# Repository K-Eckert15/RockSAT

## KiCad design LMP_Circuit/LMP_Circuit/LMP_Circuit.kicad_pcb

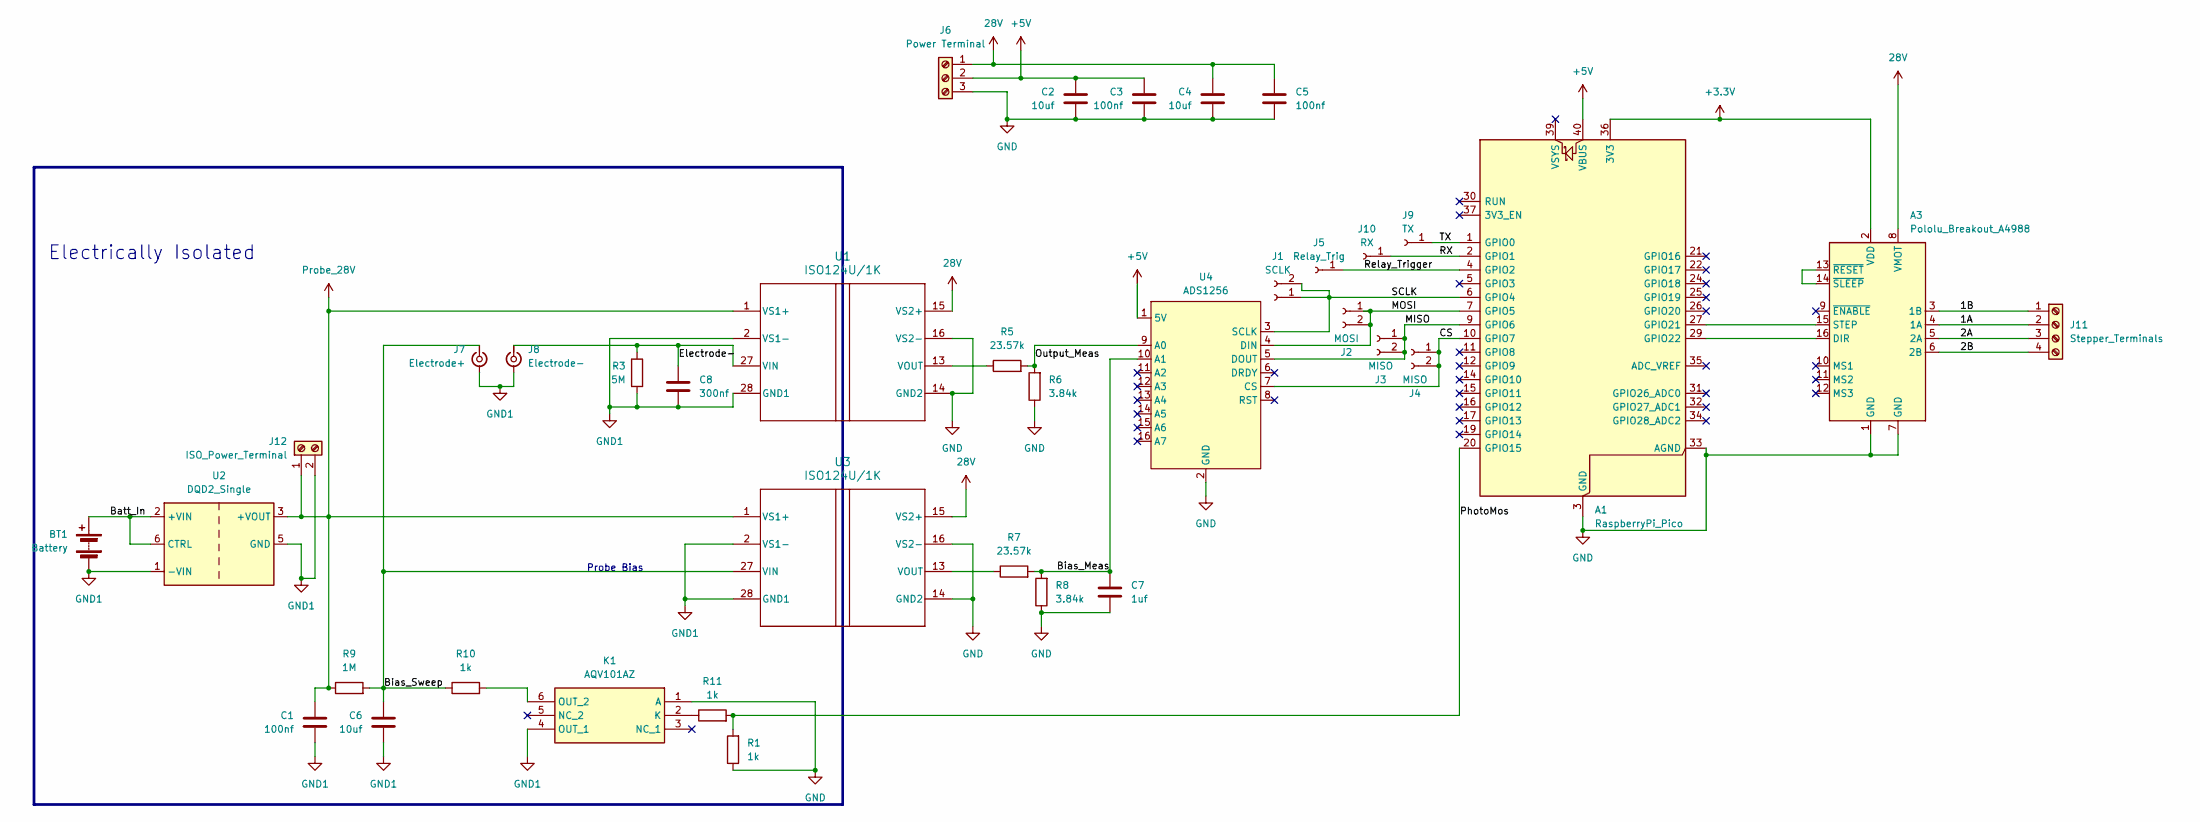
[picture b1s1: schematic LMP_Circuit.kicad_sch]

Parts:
A1: RaspberryPi_Pico; RaspberryPi_Pico_Common_Unspecified
A3: Pololu_Breakout_A4988; Pololu_Breakout-16_15.2x20.3mm
BT1: Battery; TerminalBlock_4Ucon_1x02_P3.50mm_Horizontal
C1, C3, C5: 100nf; C_0603_1608Metric; Manufacturer_Part_Number CC0603KRX7R9BB104
C2, C4, C6: 10uf; C_0603_1608Metric; Manufacturer_Part_Number GRM188R6YA106MA73D
C7: 1uf; C_0603_1608Metric; Manufacturer_Part_Number UMK107AB7105KA-T
C8: 300nf; C_0603_1608Metric; Manufacturer_Part_Number CGA3E3X7R1H334K080AB
J1: SCLK; PinHeader_1x02_P1.00mm_Vertical
J2: MOSI; PinHeader_1x02_P1.00mm_Vertical
J3, J4: MISO; PinHeader_1x02_P1.00mm_Vertical
J5: Relay_Trig; PinHeader_1x01_P1.00mm_Vertical
J6: Power Terminal; TerminalBlock_4Ucon_1x03_P3.50mm_Horizontal; Manufacturer_Part_Number 1984620
J7: Electrode+; SMA_Amphenol_901-143_Horizontal
J8: Electrode-; BNC_TEConnectivity_1478035_Horizontal
J9: TX; PinHeader_1x01_P1.00mm_Vertical
J10: RX; PinHeader_1x01_P1.00mm_Vertical
J11: Stepper_Terminals; TerminalBlock_4Ucon_1x04_P3.50mm_Horizontal; Manufacturer_Part_Number 1984633
J12: ISO_Power_Terminal; TerminalBlock_4Ucon_1x02_P3.50mm_Horizontal; Manufacturer_Part_Number ED555/2DS
K1: AQV101AZ; SOP254P960X390-6N; Mouser Part Number 769-AQV101AZ
R1, R10, R11: 1k; R_0603_1608Metric_Pad0.98x0.95mm_HandSolder; Manufacturer_Part_Number RMCF0603FT1K00
R3: 5M; R_0603_1608Metric_Pad0.98x0.95mm_HandSolder
R5, R7: 23.57k; R_0603_1608Metric_Pad0.98x0.95mm_HandSolder; Manufacturer_Part_Number RN73R1JTTD2342B25
R6, R8: 3.84k; R_0603_1608Metric_Pad0.98x0.95mm_HandSolder; Manufacturer_Part_Number ERA-3AEB3831V
R9: 1M; R_0603_1608Metric_Pad0.98x0.95mm_HandSolder; Manufacturer_Part_Number CRCW06031M00FKEA
U1, U3: ISO124U/1K; ISO124U
U2: DQD2_Single; DQD20
U4: ADS1256

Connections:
28V: A3.8 (VMOT), C4.1, C5.1, J6.1, U1.15 (VS2+), U3.15 (VS2+)
+3.3V: A1.36 (3V3), A3.2 (VDD)
+5V: A1.40 (VBUS), C2.1, C3.1, J6.2, U4.1 (5V)
/1A: A3.4 (1A), J11.2
/1B: A3.3 (1B), J11.1
/2A: A3.5 (2A), J11.3
/2B: A3.6 (2B), J11.4
/Bias_Meas: C7.2, R7.2, R8.2, U4.10 (A1)
/Bias_Sweep: C6.2, J7.1 (In), R9.2, R10.1, U3.27 (VIN)
/CS: A1.10 (GPIO7), J4.1, J4.2, U4.7 (CS)
/Electrode-: C8.2, J8.1 (In), R3.1, U1.27 (VIN)
/MISO: A1.9 (GPIO6), J3.1, J3.2, U4.5 (DOUT)
/MOSI: A1.7 (GPIO5), J2.1, J2.2, U4.4 (DIN)
/Output_Meas: R5.2, R6.2, U4.9 (A0)
/PhotoMos: A1.20 (GPIO15), R1.2, R11.2
/RX: A1.2 (GPIO1), J10.1
/Relay_Trigger: A1.4 (GPIO2), J5.1
/SCLK: A1.6 (GPIO4), J1.1, J1.2, U4.3 (SCLK)
/TX: A1.1 (GPIO0), J9.1
GND: A1.3 (GND), A1.8 (GND), A1.13 (GND), A1.18 (GND), A1.23 (GND), A1.28 (GND), A1.33 (AGND), A1.38 (GND), A3.1 (GND), A3.7 (GND), C2.2, C3.2, C4.2, C5.2, C7.1, J6.3, K1.1 (A), R1.1, R6.1, R8.1, U1.14 (GND2), U1.16 (VS2-), U3.14 (GND2), U3.16 (VS2-), U4.2 (GND)
GND1: BT1.2 (-), C1.2, C6.1, C8.1, J7.2 (Ext), J8.2 (Ext), J12.2, K1.4 (OUT_1), R3.2, U1.2 (VS1-), U1.28 (GND1), U2.1 (-VIN), U2.5 (GND), U3.2 (VS1-), U3.28 (GND1)
unnamed: A1.27 (GPIO21), A3.15 (STEP)
unnamed: A1.29 (GPIO22), A3.16 (DIR)
unnamed: A3.13 (~RESET), A3.14 (~SLEEP)
unnamed: BT1.1 (+), U2.2 (+VIN), U2.6 (CTRL)
unnamed: K1.2 (K), R11.1
unnamed: K1.6 (OUT_2), R10.2
unnamed: R5.1, U1.13 (VOUT)
unnamed: R7.1, U3.13 (VOUT)
Probe_28V: C1.1, J12.1, R9.1, U1.1 (VS1+), U2.3 (+VOUT), U3.1 (VS1+)

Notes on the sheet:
Probe Bias
Electrically Isolated

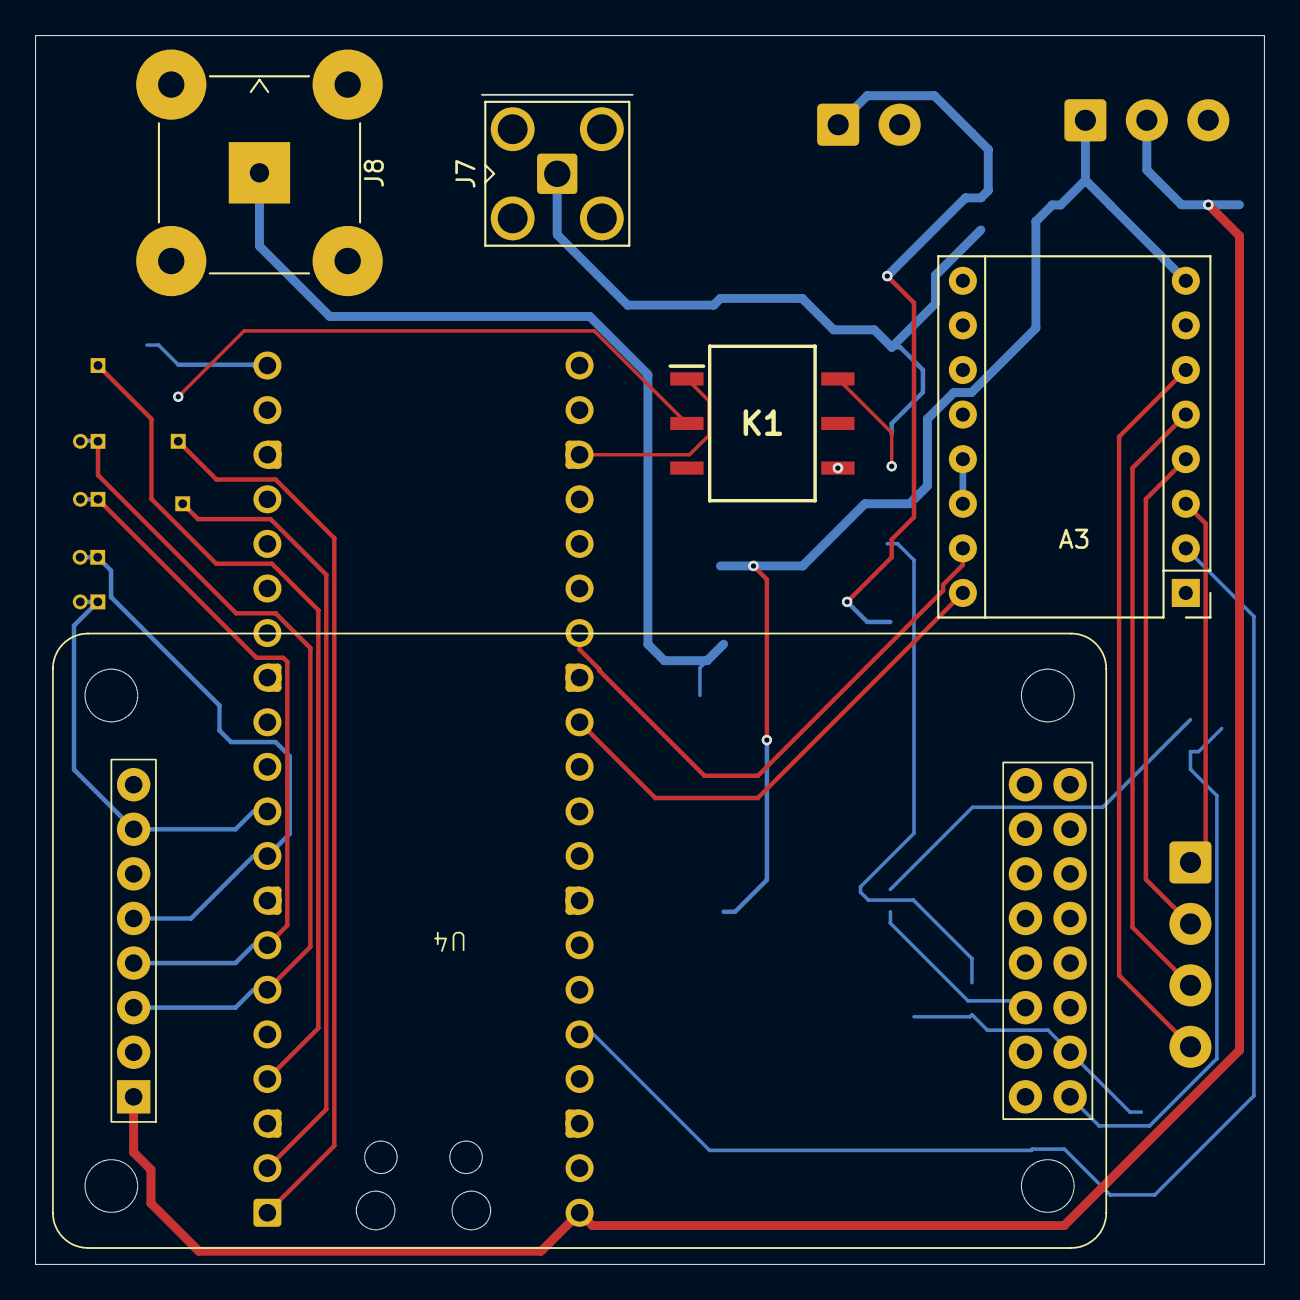
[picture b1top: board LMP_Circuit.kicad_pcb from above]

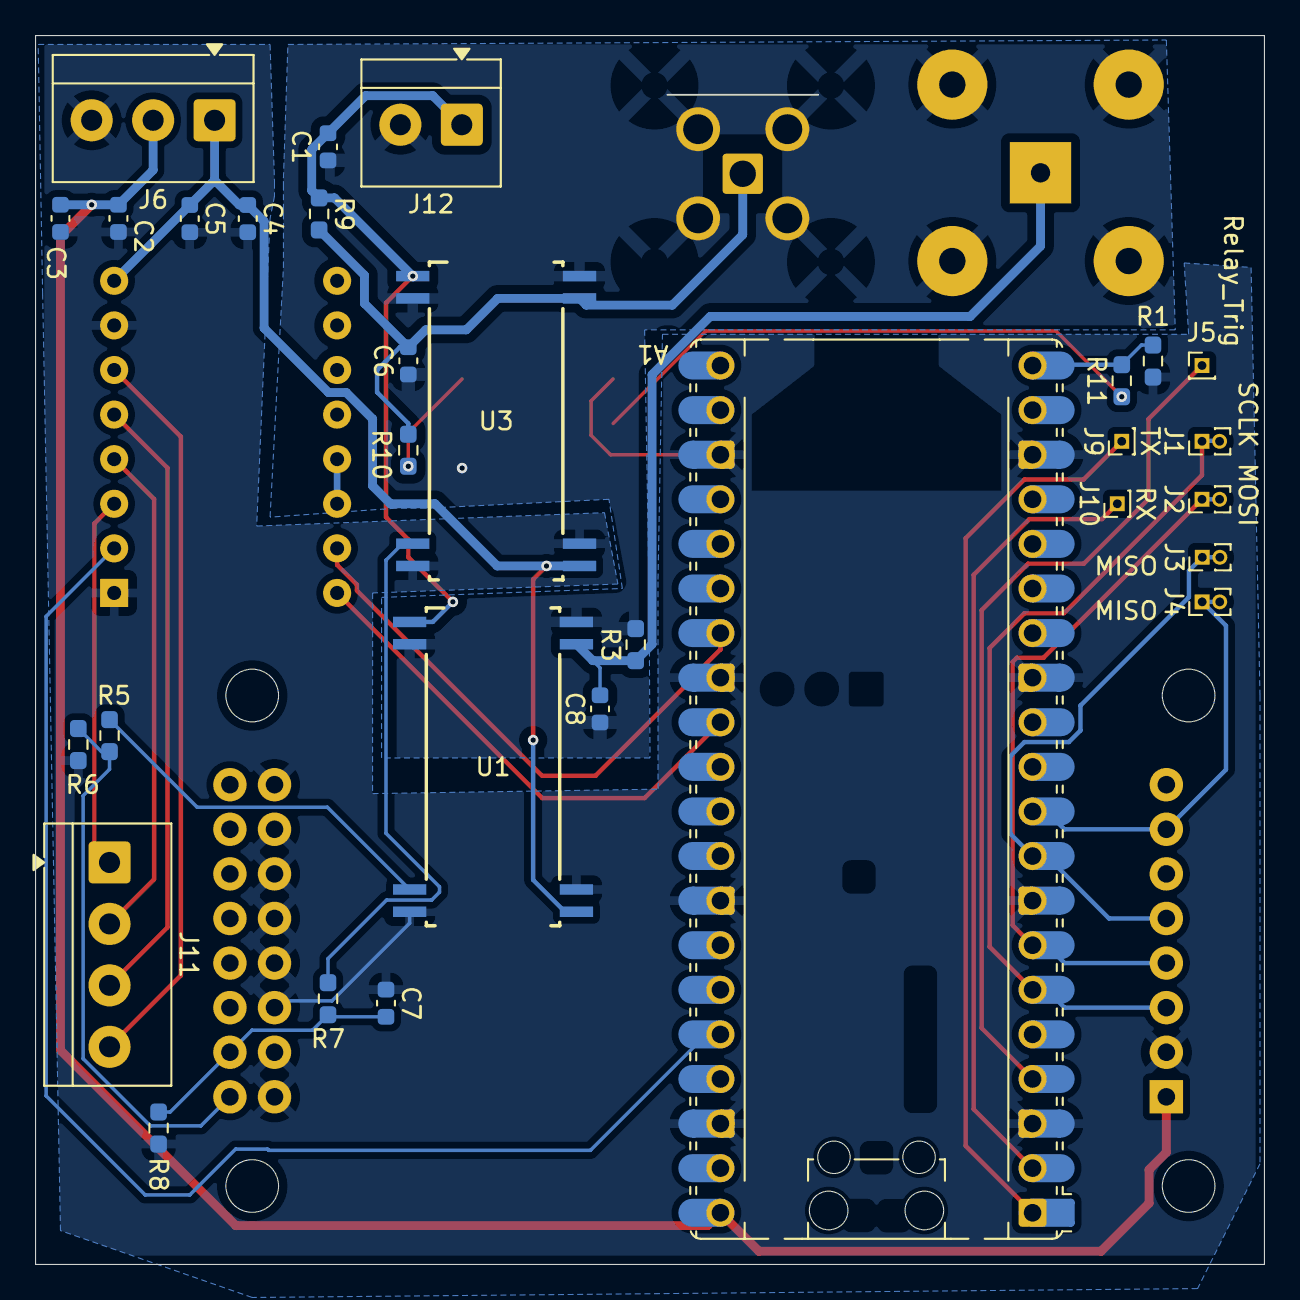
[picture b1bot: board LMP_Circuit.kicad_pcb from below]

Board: 2 copper layers, 70.0 x 70.0 mm, 35 parts (30 on the bottom side), 29 nets.

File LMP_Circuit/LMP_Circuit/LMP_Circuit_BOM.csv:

"Reference","Qty","Value","DNP","Exclude from BOM","Exclude from Board","Footprint","Datasheet","Description","Notes"
"C1,C3,C5","3","100nf","","","","Capacitor_SMD:C_0603_1608Metric","https://yageogroup.com/content/datasheet/asset/file/UPY-GPHC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","CC0603KRX7R9BB104,Unpolarized capacitor",""
"C2,C4,C6","3","10uf","","","","Capacitor_SMD:C_0603_1608Metric","https://search.murata.co.jp/Ceramy/image/img/A01X/G101/ENG/G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","GRM188R6YA106MA73D",""
"C7","1","1uf","","","","Capacitor_SMD:C_0603_1608Metric","https://mm.digikey.com/Volume0/opasdata/d220001/medias/docus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","UMK107AB7105KA-T",""
"C8","1","300nf","","","","Capacitor_SMD:C_0603_1608Metric","https://product.tdk.com/system/files/dam/doc/product/capacit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","CGA3E3X7R1H334K080AB","330nf"
"J6","1","Power Terminal","","","","TerminalBlock_4Ucon:TerminalBlock_4Ucon_1x03_P3.50mm_Horizontal","https://mm.digikey.com/Volume0/opasdata/d220001/medias/docus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","1984620",""
"J7","1","Electrode+","","","","Connector_Coaxial:SMA_Amphenol_901-143_Horizontal","~","",""
"J8","1","Electrode-","","","","Connector_Coaxial:BNC_TEConnectivity_1478035_Horizontal","~","",""
"J11","1","Stepper_Terminals","","","","TerminalBlock_4Ucon:TerminalBlock_4Ucon_1x04_P3.50mm_Horizontal","https://mm.digikey.com/Volume0/opasdata/d220001/medias/docus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","1984633",""
"J12","1","ISO_Power_Terminal","","","","TerminalBlock_4Ucon:TerminalBlock_4Ucon_1x02_P3.50mm_Horizontal","","ED555/2DS",""
"K1","1","AQV101AZ","","","","AQV101AZ:SOP254P960X390-6N","https://mm.digikey.com/Volume0/opasdata/d220001/medias/docus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","AQV101AZ",""
"R1,R10,R11","3","1k","","","","Resistor_SMD:R_0603_1608Metric_Pad0.98x0.95mm_HandSolder","https://www.seielect.com/catalog/SEI-RMCF_RMCP.pdf","RMCF0603FT1K00",""
"R3","1","5M","","","","Resistor_SMD:R_0603_1608Metric_Pad0.98x0.95mm_HandSolder","~","","Might switch with 3M"
"R5,R7","2","23.57k","","","","Resistor_SMD:R_0603_1608Metric_Pad0.98x0.95mm_HandSolder","https://www.koaspeer.com/pdfs/RN73R.pdf","RN73R1JTTD2342B25","23.4 kOhms"
"R6,R8","2","3.84k","","","","Resistor_SMD:R_0603_1608Metric_Pad0.98x0.95mm_HandSolder","https://industrial.panasonic.com/cdbs/www-data/pdf/RDM0000/A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","ERA-3AEB3831V","3.83k"
"R9","1","1M","","","","Resistor_SMD:R_0603_1608Metric_Pad0.98x0.95mm_HandSolder","https://www.vishay.com/docs/20035/dcrcwe3.pdf","CRCW06031M00FKEA",""
"U1,U3","2","ISO124U/1K","","","","External/Custom Parts:ISO124U","https://www.ti.com/lit/gpn/iso124","",""
"U2","1","DQD2_Single","","","Excluded from board","External/Custom Parts:DQD20","https://www.belfuse.com/media/datasheets/products/power-supp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","",""
"U4","1","ADS1256","","","","External/Custom Parts:ADS1256","","",""

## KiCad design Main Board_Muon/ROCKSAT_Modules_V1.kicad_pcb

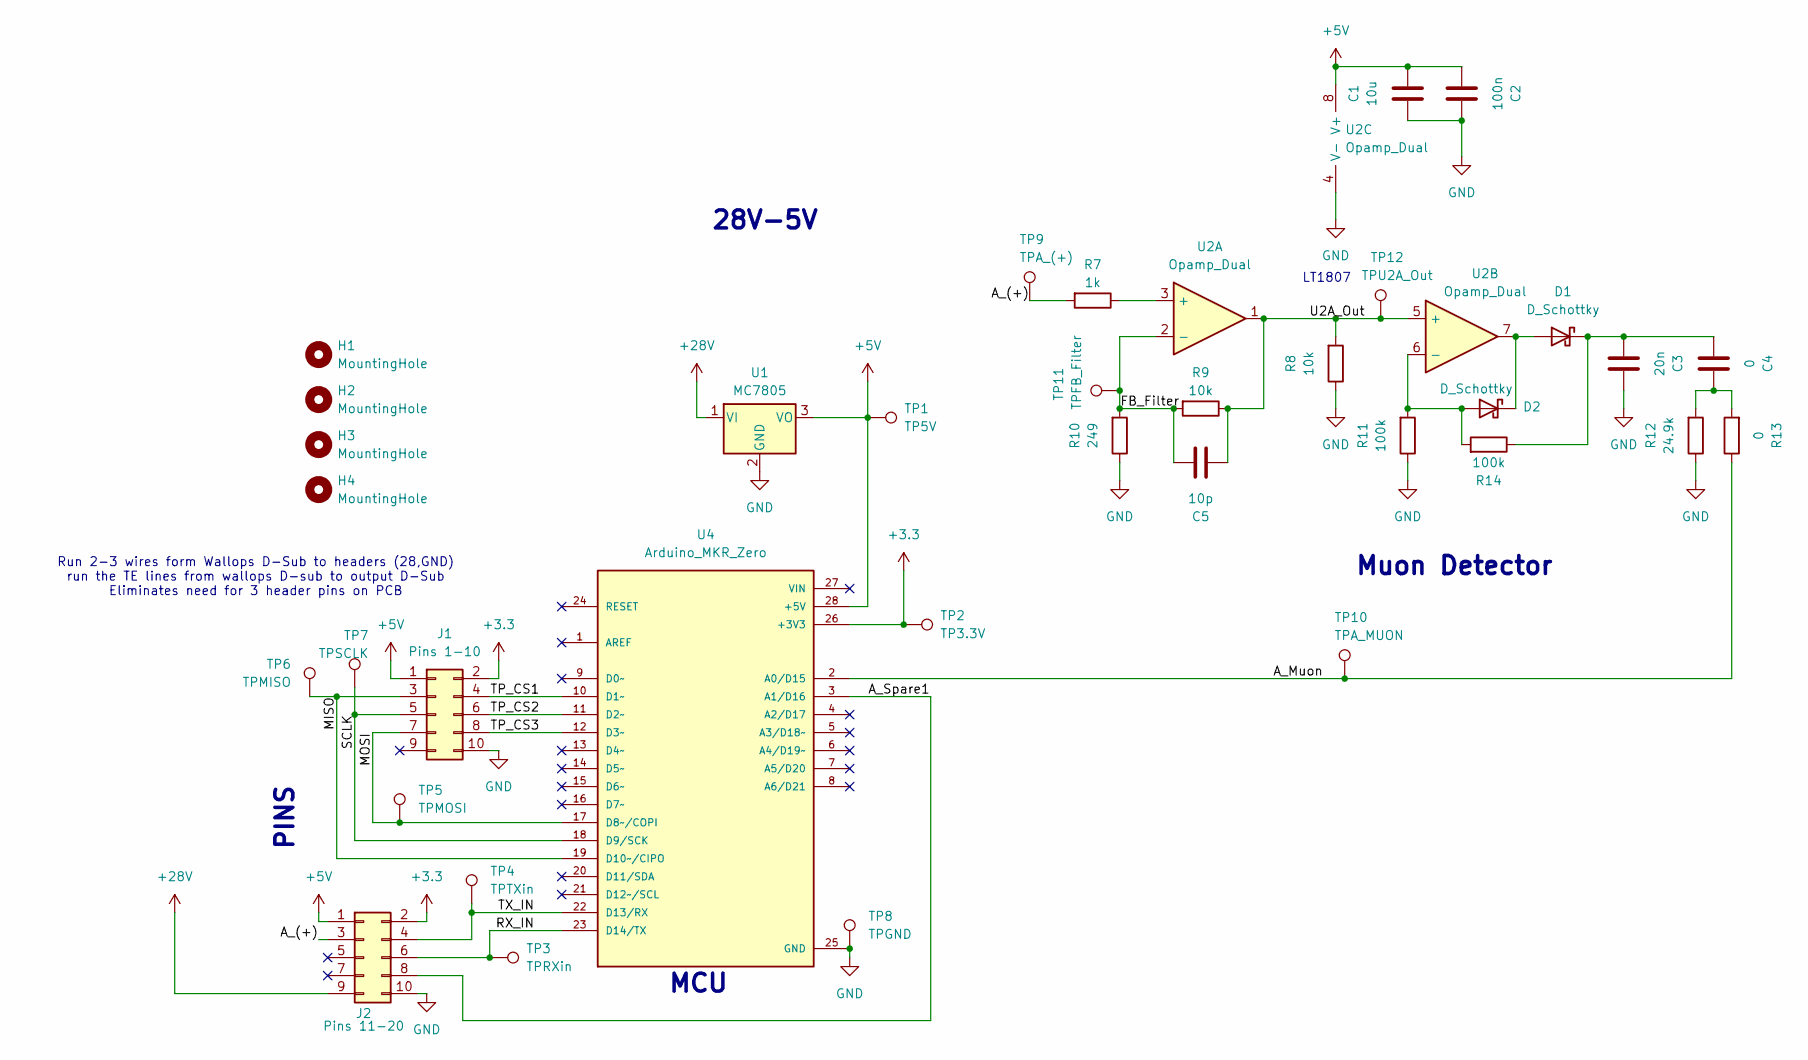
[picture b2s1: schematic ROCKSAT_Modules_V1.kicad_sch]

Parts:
C1: 10u; C_Disc_D3.8mm_W2.6mm_P2.50mm
C2: 100n; C_Disc_D3.8mm_W2.6mm_P2.50mm
C3: 20n; C_Disc_D3.8mm_W2.6mm_P2.50mm
C4: 0; C_Disc_D3.8mm_W2.6mm_P2.50mm
C5: 10p; C_Disc_D3.8mm_W2.6mm_P2.50mm
D1, D2: D_Schottky; D_A-405_P10.16mm_Horizontal
H1, H2, H3, H4: MountingHole; MountingHole_3.2mm_M3
J1: Pins 1-10; PinSocket_2x05_P2.54mm_Vertical
J2: Pins 11-20; PinSocket_2x05_P2.54mm_Vertical
R7: 1k; R_Axial_DIN0207_L6.3mm_D2.5mm_P7.62mm_Horizontal
R8, R9: 10k; R_Axial_DIN0207_L6.3mm_D2.5mm_P7.62mm_Horizontal
R10: 249; R_Axial_DIN0207_L6.3mm_D2.5mm_P7.62mm_Horizontal
R11, R14: 100k; R_Axial_DIN0207_L6.3mm_D2.5mm_P7.62mm_Horizontal
R12: 24.9k; R_Axial_DIN0207_L6.3mm_D2.5mm_P7.62mm_Horizontal
R13: 0; R_Axial_DIN0207_L6.3mm_D2.5mm_P7.62mm_Horizontal
TP1: TP5V; TestPoint_THTPad_D1.5mm_Drill0.7mm
TP2: TP3.3V; TestPoint_THTPad_D1.5mm_Drill0.7mm
TP3: TPRXin; TestPoint_THTPad_D1.5mm_Drill0.7mm
TP4: TPTXin; TestPoint_THTPad_D1.5mm_Drill0.7mm
TP5: TPMOSI; TestPoint_THTPad_D1.5mm_Drill0.7mm
TP6: TPMISO; TestPoint_THTPad_D1.5mm_Drill0.7mm
TP7: TPSCLK; TestPoint_THTPad_D1.5mm_Drill0.7mm
TP8: TPGND; TestPoint_THTPad_D1.5mm_Drill0.7mm
TP9: TPA_(+); TestPoint_THTPad_D1.5mm_Drill0.7mm
TP10: TPA_MUON; TestPoint_THTPad_D1.5mm_Drill0.7mm
TP11: TPFB_Filter; TestPoint_THTPad_D1.5mm_Drill0.7mm
TP12: TPU2A_Out; TestPoint_THTPad_D1.5mm_Drill0.7mm
U1: MC7805; TO-220-3_Horizontal_TabDown
U2: Opamp_Dual; SOIC-8_3.9x4.9mm_P1.27mm
U4: Arduino_MKR_Zero; MODULE_ABX00011; PARTREV 02/04/2020

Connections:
+3.3: J1.2, J2.2, TP2.1, U4.26 (+3V3)
+5V: C1.2, C2.2, J1.1, J2.1, TP1.1, U1.3 (VO), U2.8 (V+), U4.28 (+5V)
+28V: J2.9, U1.1 (VI)
/A_(+): J2.3, R7.2, TP9.1
/A_Muon: R13.1, TP10.1, U4.2 (A0/D15)
/A_Spare1: J2.8, U4.3 (A1/D16)
/FB_Filter: C5.1, R9.2, R10.2, TP11.1, U2.2 (-)
/MISO: J1.3, TP6.1, U4.19 (D10~/CIPO)
/MOSI: J1.7, TP5.1, U4.17 (D8~/COPI)
/RX_IN: J2.6, TP3.1, U4.23 (D14/TX)
/SCLK: J1.5, TP7.1, U4.18 (D9/SCK)
/TP_CS1: J1.4, U4.10 (D1~)
/TP_CS2: J1.6, U4.11 (D2~)
/TP_CS3: J1.8, U4.12 (D3~)
/TX_IN: J2.4, TP4.1, U4.22 (D13/RX)
/U2A_Out: C5.2, R8.2, R9.1, TP12.1, U2.1, U2.5 (+)
GND: C1.1, C2.1, C3.1, J1.10, J2.10, R8.1, R10.1, R11.1, R12.1, TP8.1, U1.2 (GND), U2.4 (V-), U4.25 (GND)
unnamed: C4.1, R12.2, R13.2
unnamed: D1.2 (A), D2.1 (K), U2.7
unnamed: C3.2, C4.2, D1.1 (K), R14.1
unnamed: D2.2 (A), R11.2, R14.2, U2.6 (-)
unnamed: R7.1, U2.3 (+)

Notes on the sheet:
Run 2-3 wires form Wallops D-Sub to headers (28,GND) run the TE lines from wallops D-sub to output D-Sub Eliminates need for 3 header pins on PCB
LT1807
MCU
28V-5V
Muon Detector
PINS

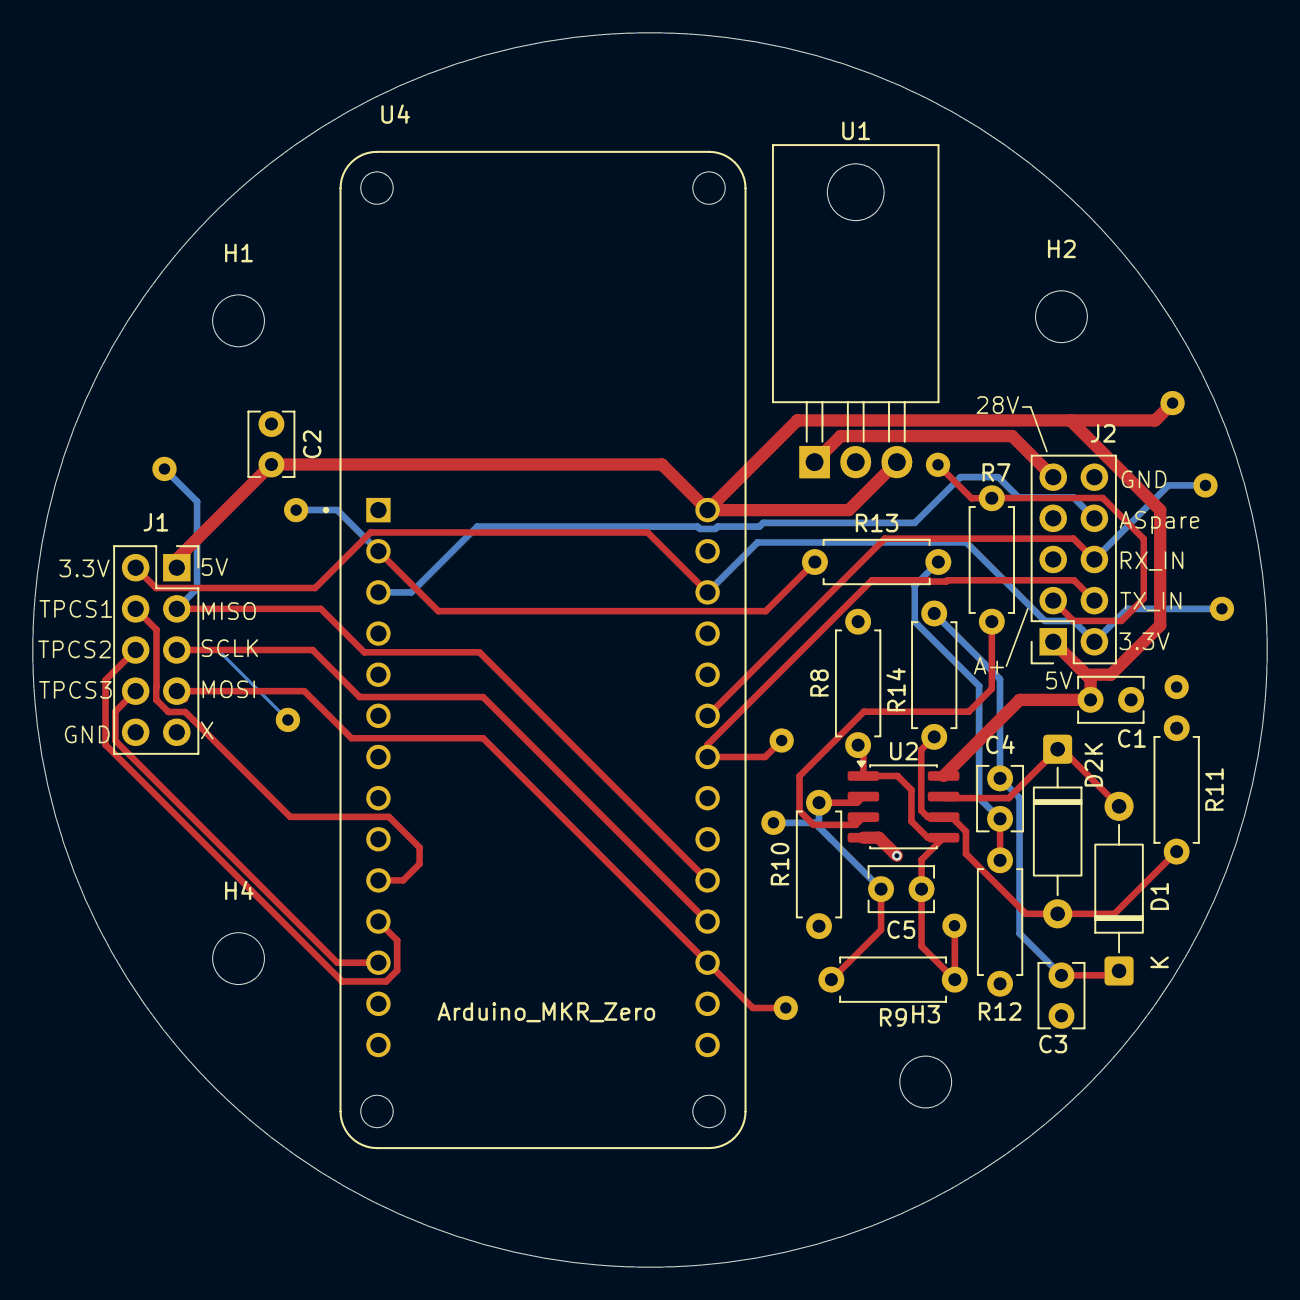
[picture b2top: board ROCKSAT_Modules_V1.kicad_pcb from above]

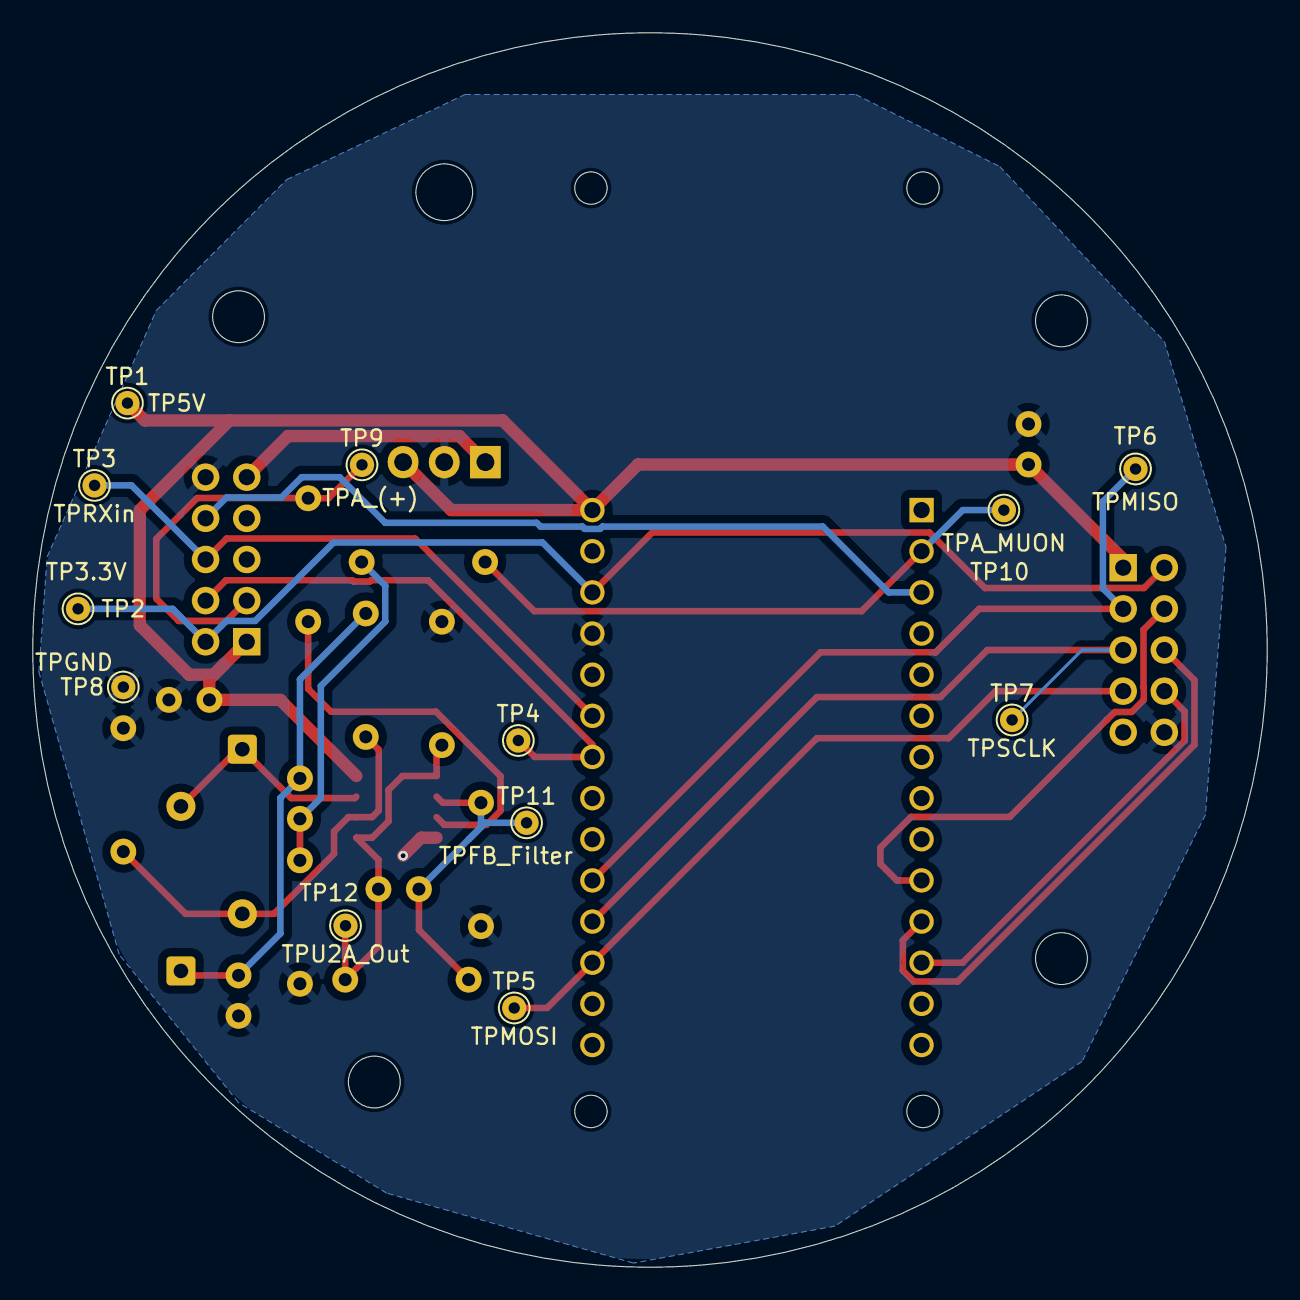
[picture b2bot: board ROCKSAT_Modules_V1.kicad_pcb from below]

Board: 2 copper layers, 76.2 x 76.2 mm, 36 parts (12 on the bottom side), 22 nets.

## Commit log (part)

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2026-02-25 Initializing Files
    Added Main Board
2026-02-25 Created Files
2026-02-26 mounting holes fixed. Mosfet Tab Down. Module Ready.
2026-02-26 ADC, MCU, and Driver Added
2026-03-05 Test Points Added
2026-03-05 gerber files generated
2026-03-08 added power converter diagram and relay.
2026-03-12 schematic near completion. Most likely functional.
2026-03-12 initial layout created.
2026-03-12 Fully routed, lacks photomosfet
2026-03-13 Added Photomos. finished layout
2026-03-13 Gerber Files created
2026-03-13 finished PCB layout with Photomos
2026-03-13 Electrode Added and Gerber files produced.
2026-03-13 Zip files created
2026-03-18 SiPM Gerber Files
2026-03-22 BOM Updates
2026-03-22 BOM Completed 3-22-26
2026-03-22 BOM Exported
2026-03-23 LMP BOM updates
2026-03-23 LMP BOM started
2026-03-28 sipm BOM added, files organized a bit more
2026-03-28 BOM Addeed
2026-04-01 Main Board and SiPM board Parts List
2026-04-01 Rename 2026-04-01T121725.csv to Main and SiPM BOM.csv
2026-04-03 D-Sub added
2026-04-03 Male D-sub added
2026-04-10 Updated BOM
2026-04-10 added qtys
